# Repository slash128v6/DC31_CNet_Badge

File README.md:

# DC31_CNet_Badge

See the Docs folder

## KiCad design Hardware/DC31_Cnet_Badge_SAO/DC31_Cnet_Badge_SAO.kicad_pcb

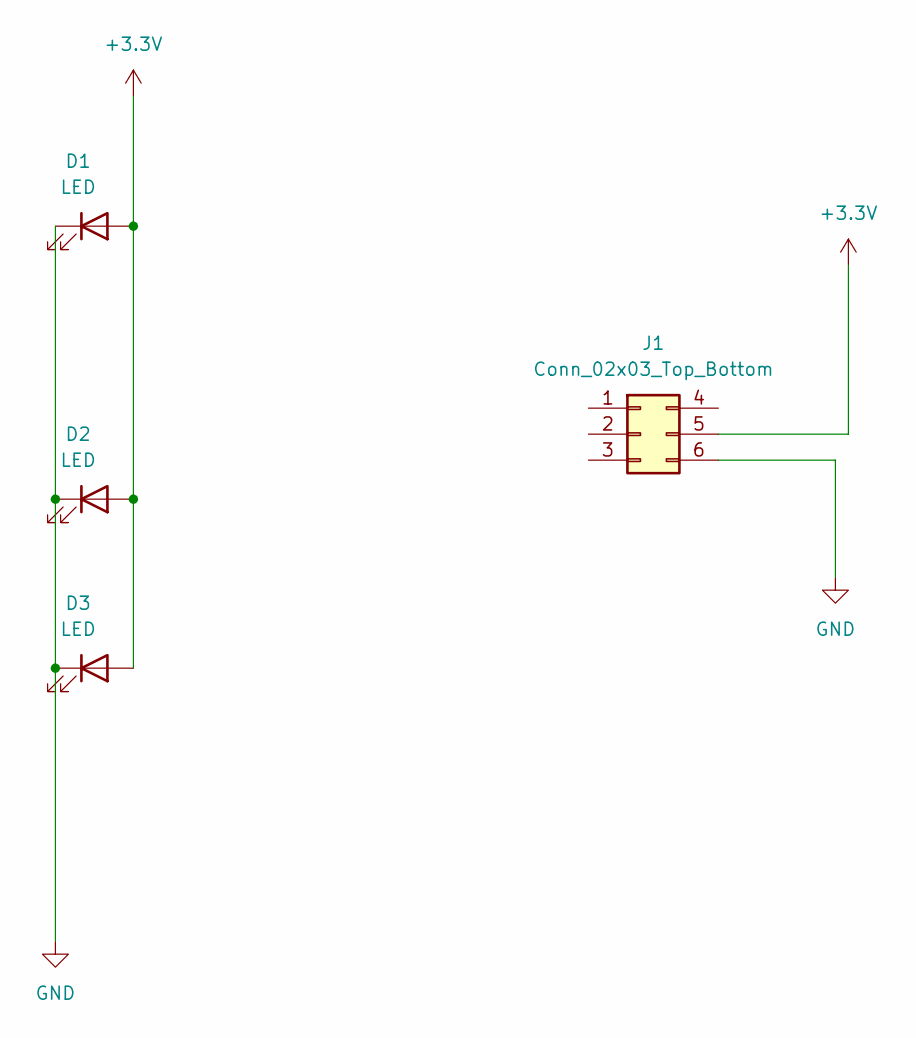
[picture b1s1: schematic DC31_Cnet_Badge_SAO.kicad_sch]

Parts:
D1, D2, D3: LED; LED_D3.0mm
J1: Conn_02x03_Top_Bottom; PinSocket_2x03_P2.54mm_Vertical_Tab

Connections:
+3.3V: D1.2 (A), D2.2 (A), D3.2 (A), J1.5
GND: D1.1 (K), D2.1 (K), D3.1 (K), J1.6

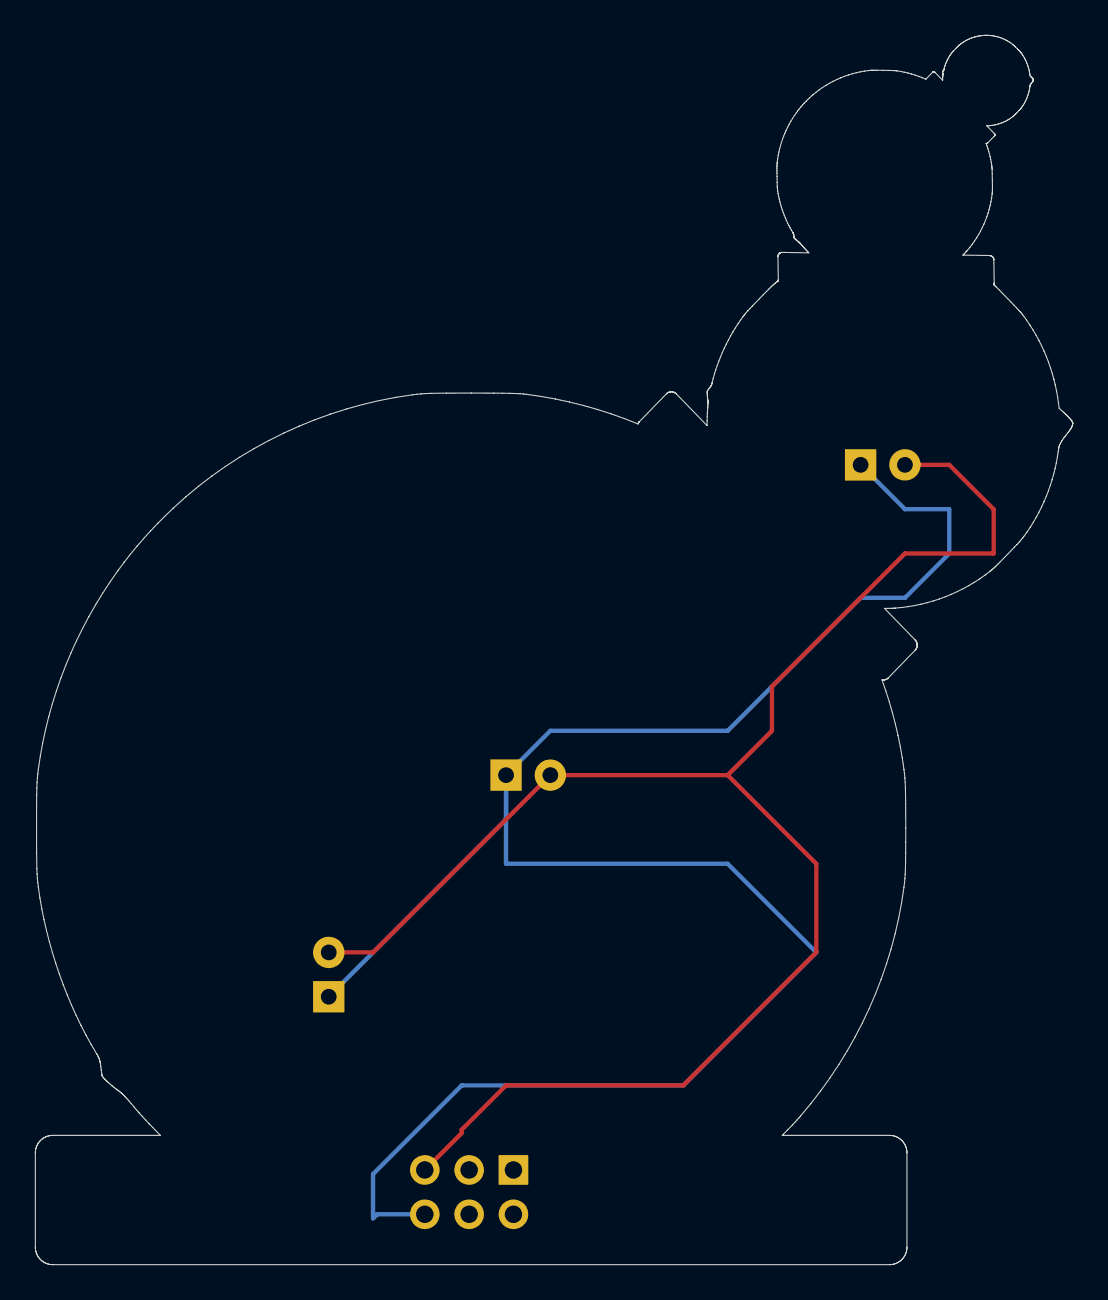
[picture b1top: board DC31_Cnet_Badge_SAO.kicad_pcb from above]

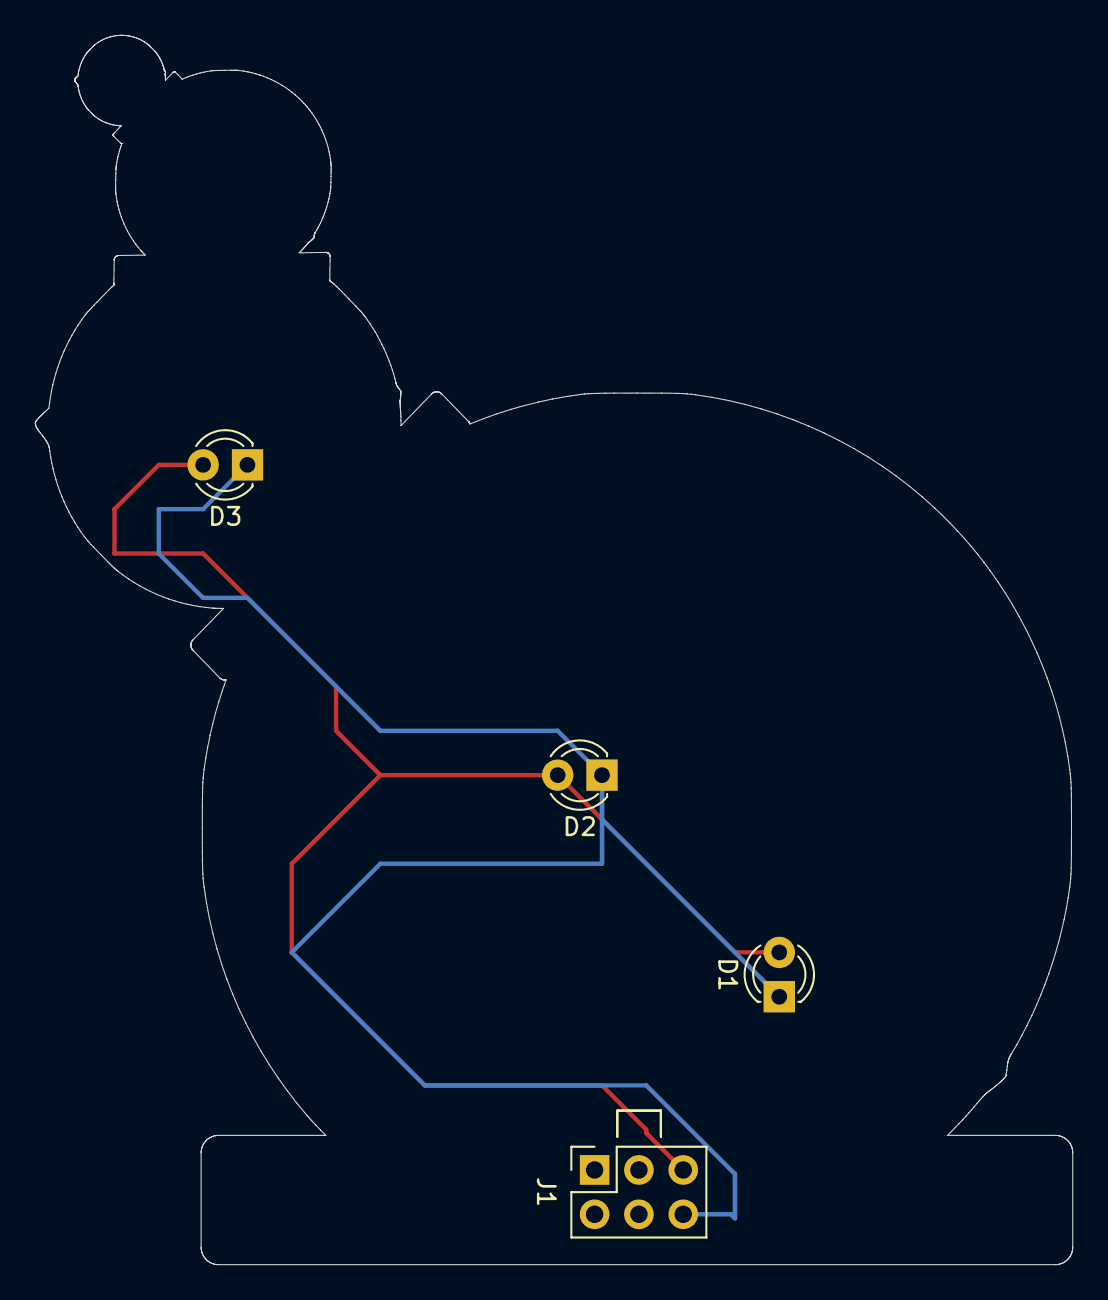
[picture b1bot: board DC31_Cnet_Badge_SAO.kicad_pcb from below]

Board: 2 copper layers, 59.5 x 70.5 mm, 4 parts (4 on the bottom side), 2 nets.

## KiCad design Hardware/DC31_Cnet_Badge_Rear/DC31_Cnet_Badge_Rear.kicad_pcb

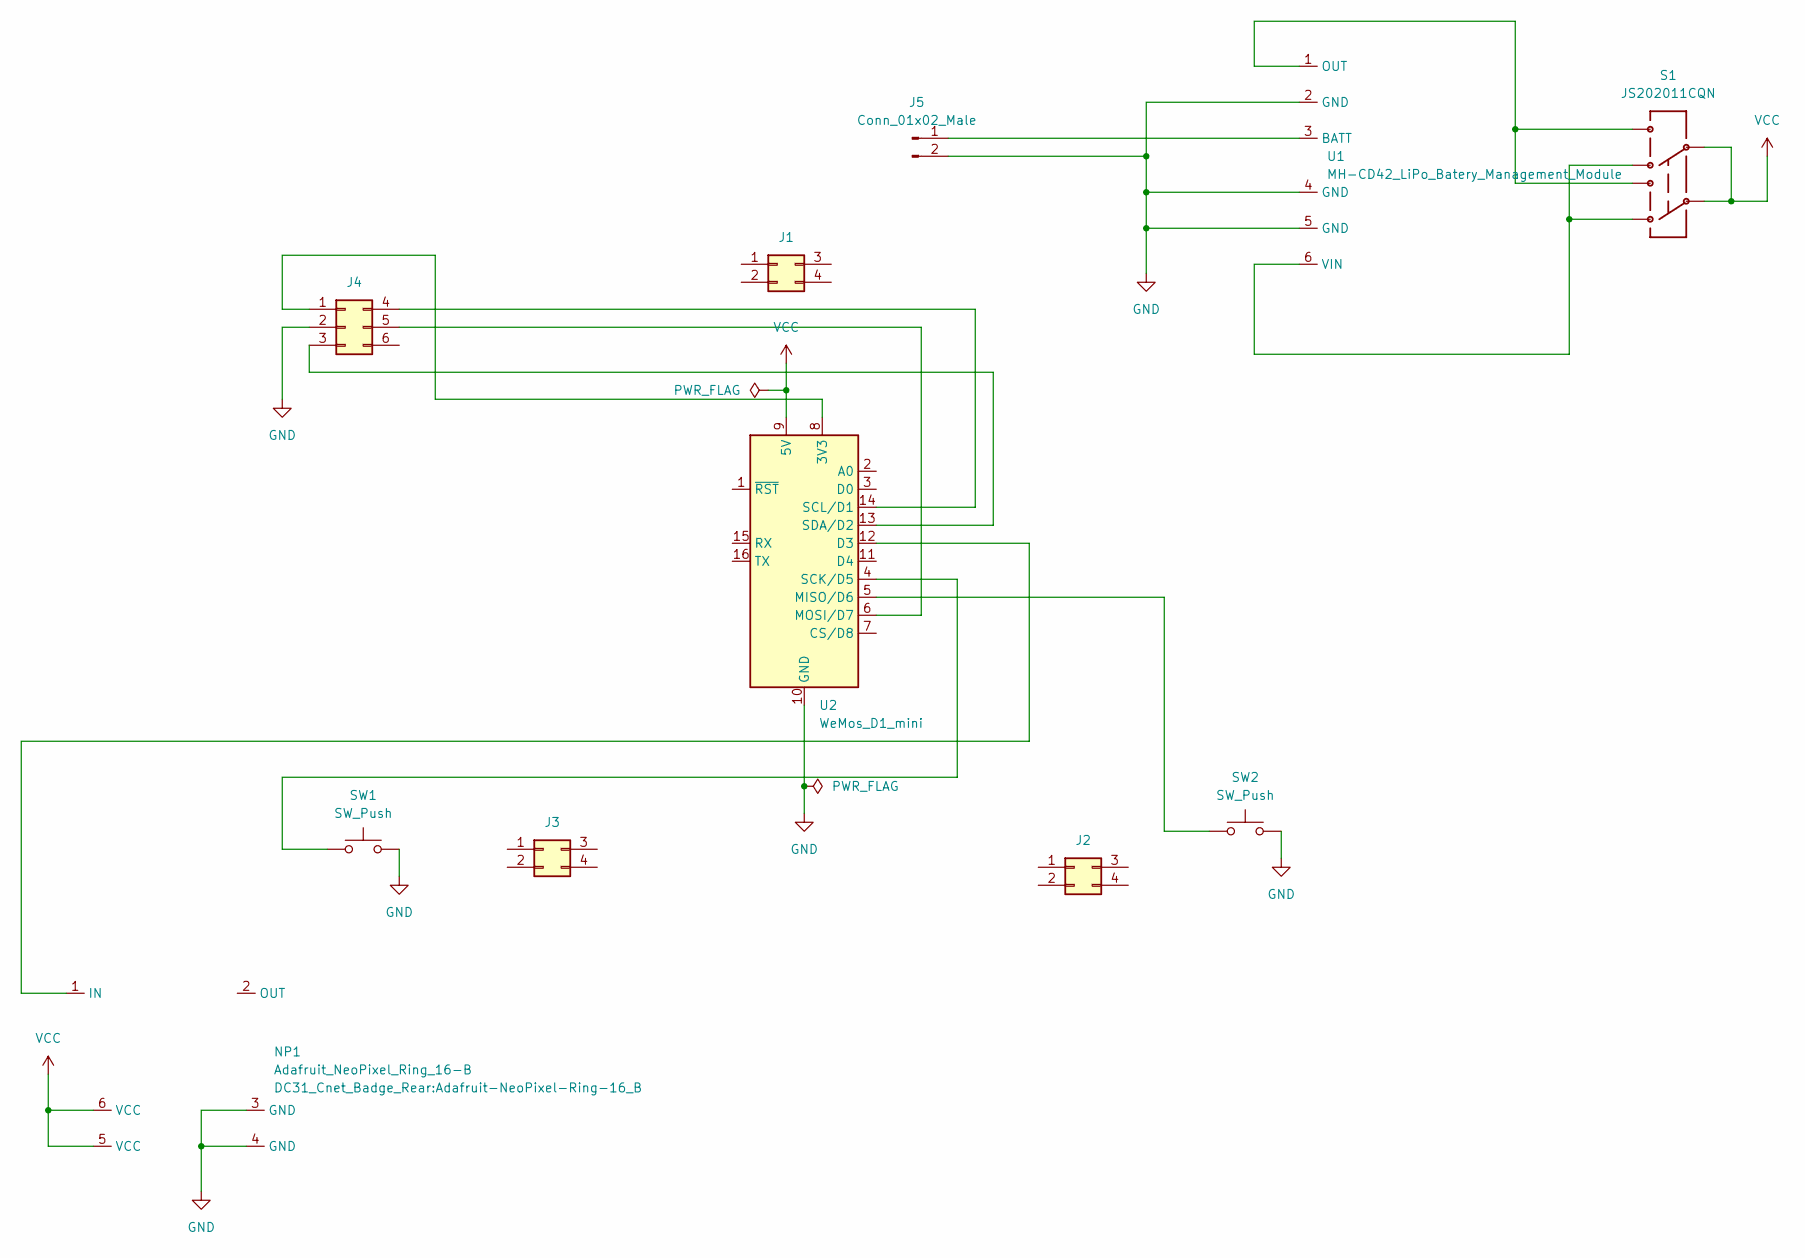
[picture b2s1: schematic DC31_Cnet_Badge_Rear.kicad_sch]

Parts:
J1, J2, J3: Conn_02x02_Top_Bottom; PinSocket_2x02_P2.54mm_Vertical
J4: Conn_02x03_Top_Bottom; PinSocket_2x03_P2.54mm_Vertical_Tab
J5: Conn_01x02_Male; JST_PH_S2B-PH-K_1x02_P2.00mm_Horizontal
NP1: Adafruit_NeoPixel_Ring_16-B; Adafruit-NeoPixel-Ring-16_B
S1: JS202011CQN; SPARKFUN-RETIRED_SWITCH-2.5X3.2-6
SW1, SW2: SW_Push; SW_PUSH_6mm
U1: MH-CD42_LiPo_Batery_Management_Module; MH-CD42 LiPo Battery Management Module Rear Charge LEDs
U2: WeMos_D1_mini; WEMOS_D1_mini_light

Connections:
GND: J4.2, J5.2, NP1.3 (GND), NP1.4 (GND), SW1.2, SW2.2, U1.2 (GND), U1.4 (GND), U1.5 (GND), U2.10 (GND)
unnamed: J4.1, U2.8 (3V3)
unnamed: J4.3, U2.13 (SDA/D2)
unnamed: J4.4, U2.14 (SCL/D1)
unnamed: J4.5, U2.6 (MOSI/D7)
unnamed: J5.1, U1.3 (BATT)
unnamed: NP1.1 (IN), U2.12 (D3)
unnamed: S1.1, S1.4, U1.6 (VIN)
unnamed: S1.3, S1.6, U1.1 (OUT)
unnamed: SW1.1, U2.4 (SCK/D5)
unnamed: SW2.1, U2.5 (MISO/D6)
VCC: NP1.5 (VCC), NP1.6 (VCC), S1.2, S1.5, U2.9 (5V)

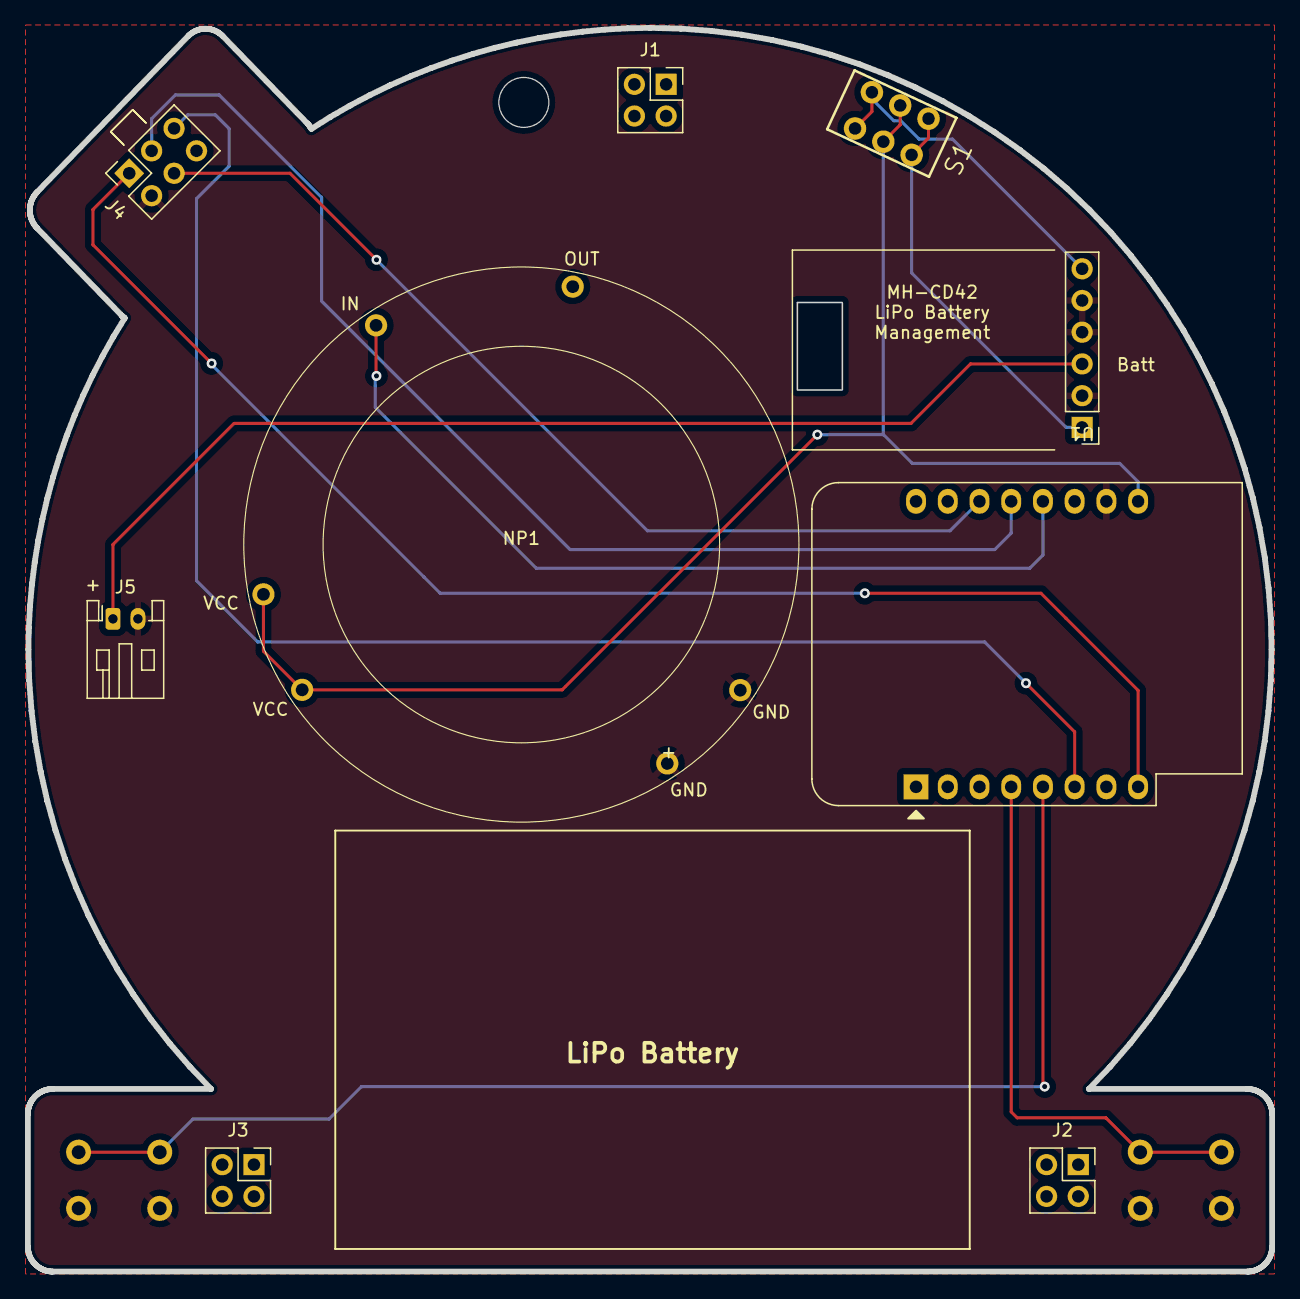
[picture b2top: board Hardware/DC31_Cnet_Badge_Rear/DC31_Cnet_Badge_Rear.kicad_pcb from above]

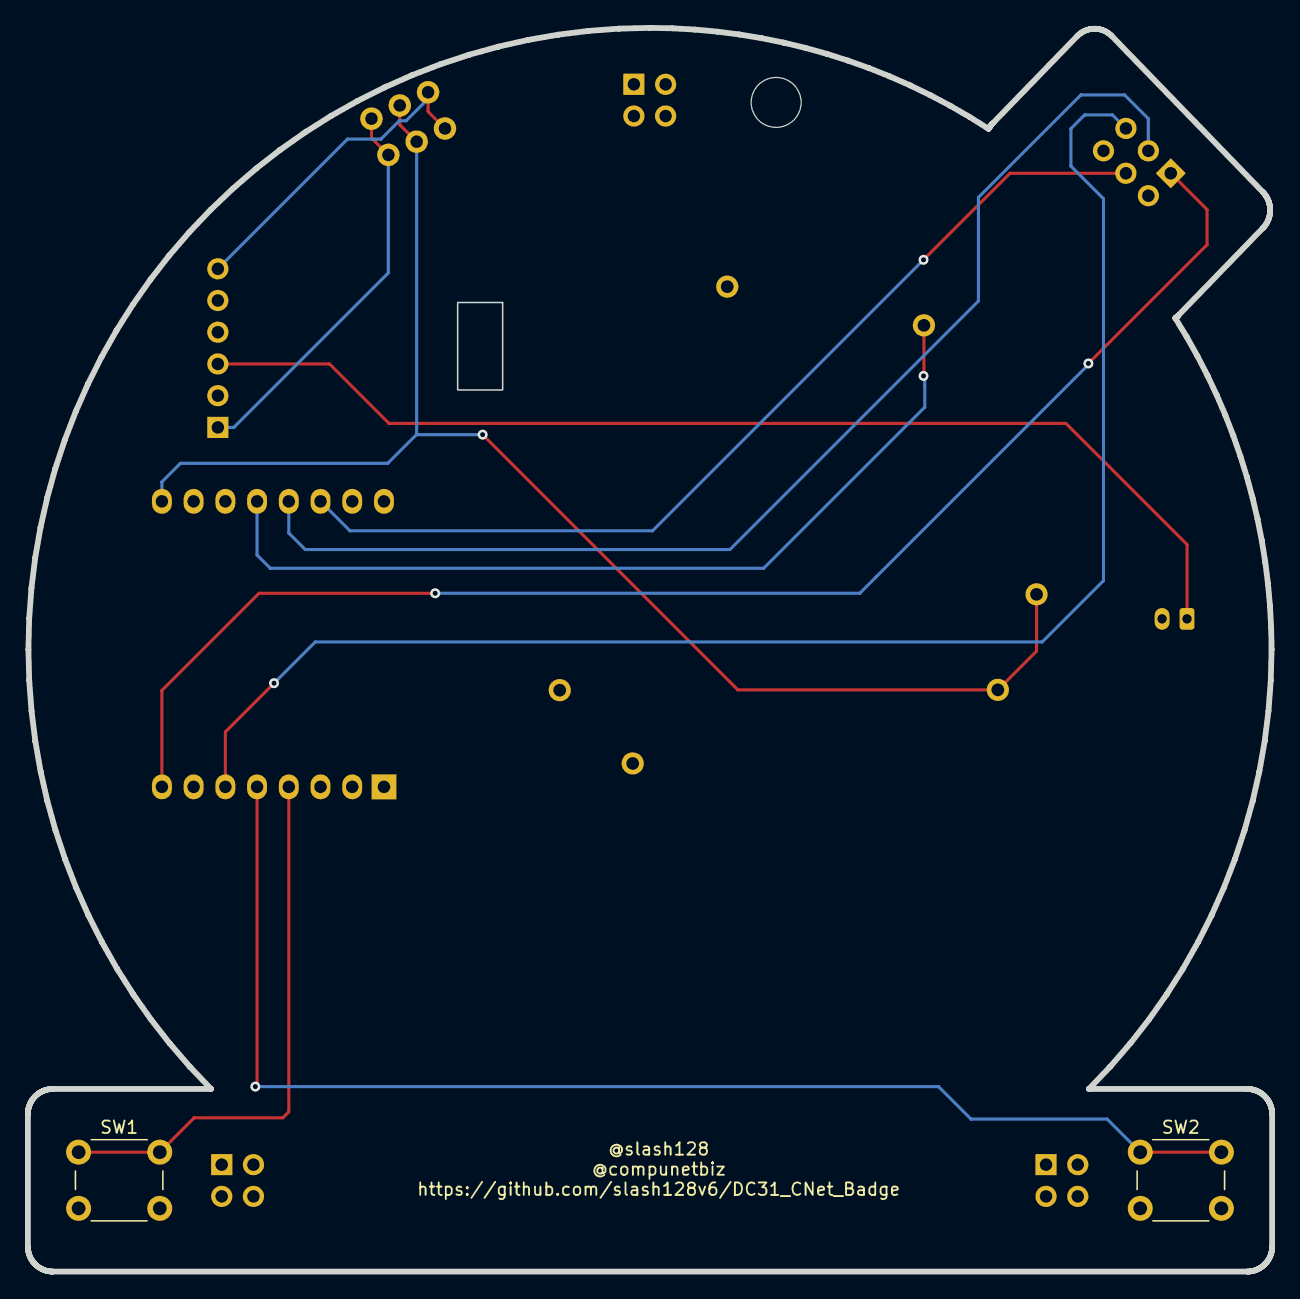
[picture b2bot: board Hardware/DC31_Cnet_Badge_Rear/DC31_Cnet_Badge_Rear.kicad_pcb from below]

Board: 2 copper layers, 99.6 x 99.6 mm, 11 parts (2 on the bottom side), 12 nets.

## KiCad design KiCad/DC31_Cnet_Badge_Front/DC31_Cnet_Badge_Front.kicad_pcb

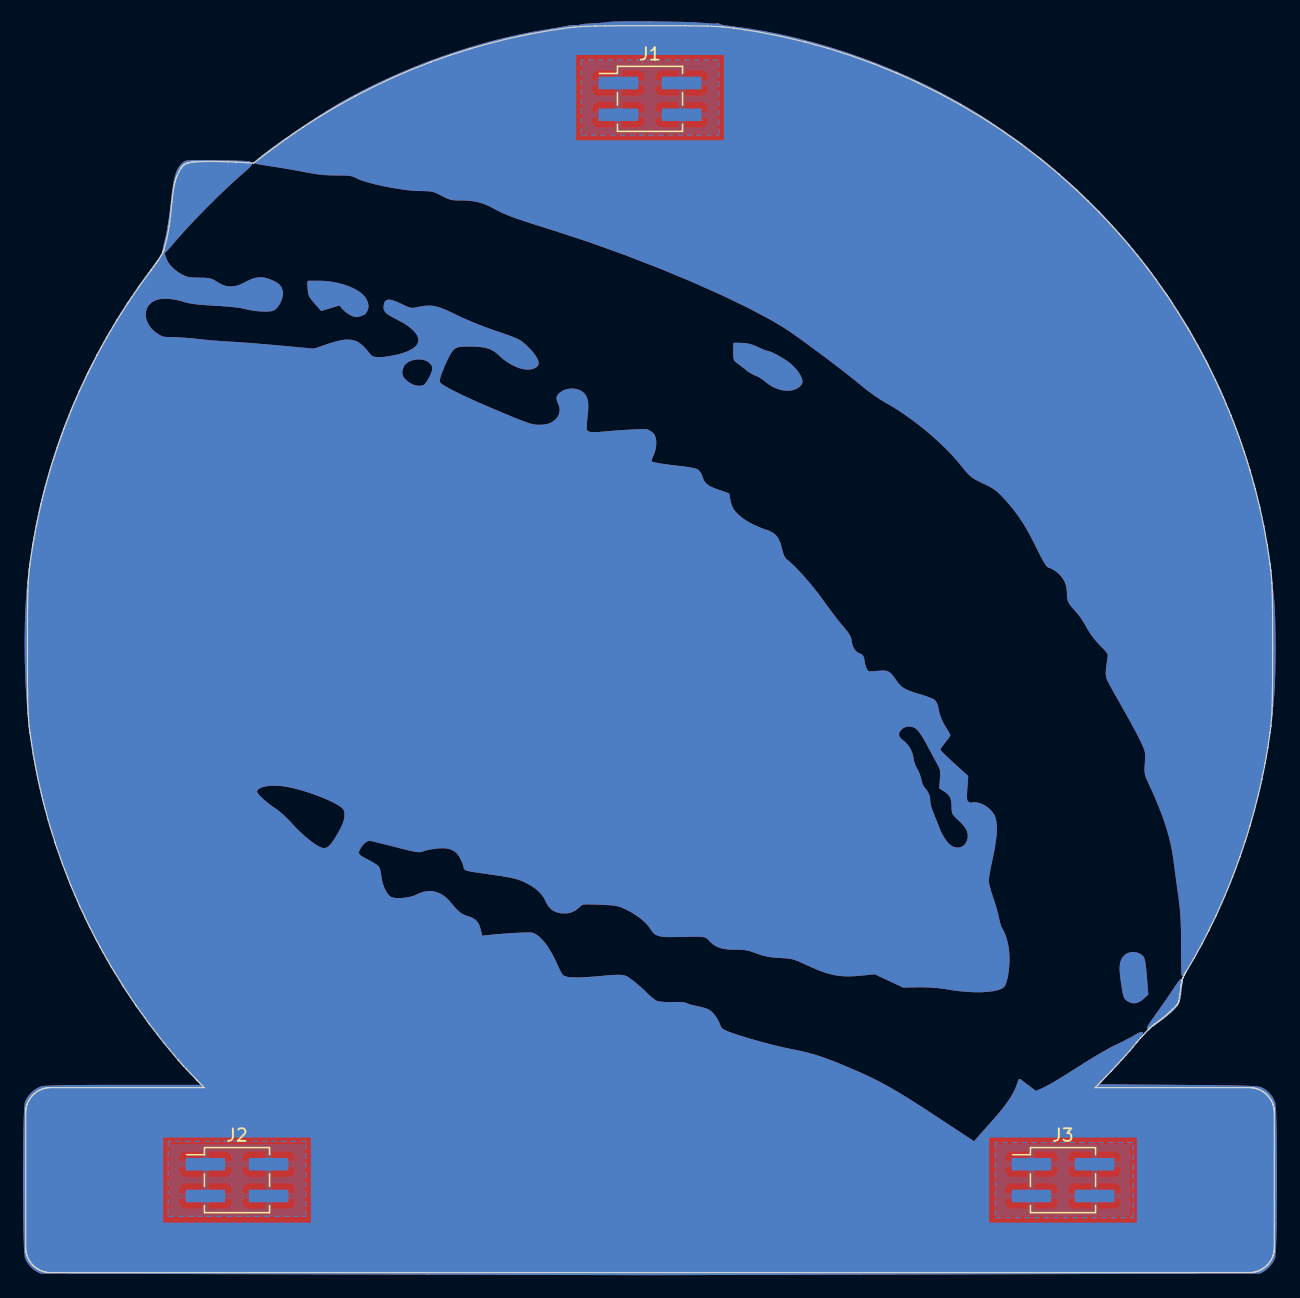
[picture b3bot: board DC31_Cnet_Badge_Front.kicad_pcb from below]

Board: 2 copper layers, 99.8 x 99.6 mm, 3 parts (3 on the bottom side), 3 nets, no tracks yet.

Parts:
J1, J2, J3: Conn_02x02_Top_Bottom; PinHeader_2x02_P2.54mm_Vertical_SMD

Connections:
/J1: J1.1, J1.2, J1.3, J1.4
/J2: J2.1, J2.2, J2.3, J2.4
/J3: J3.1, J3.2, J3.3, J3.4

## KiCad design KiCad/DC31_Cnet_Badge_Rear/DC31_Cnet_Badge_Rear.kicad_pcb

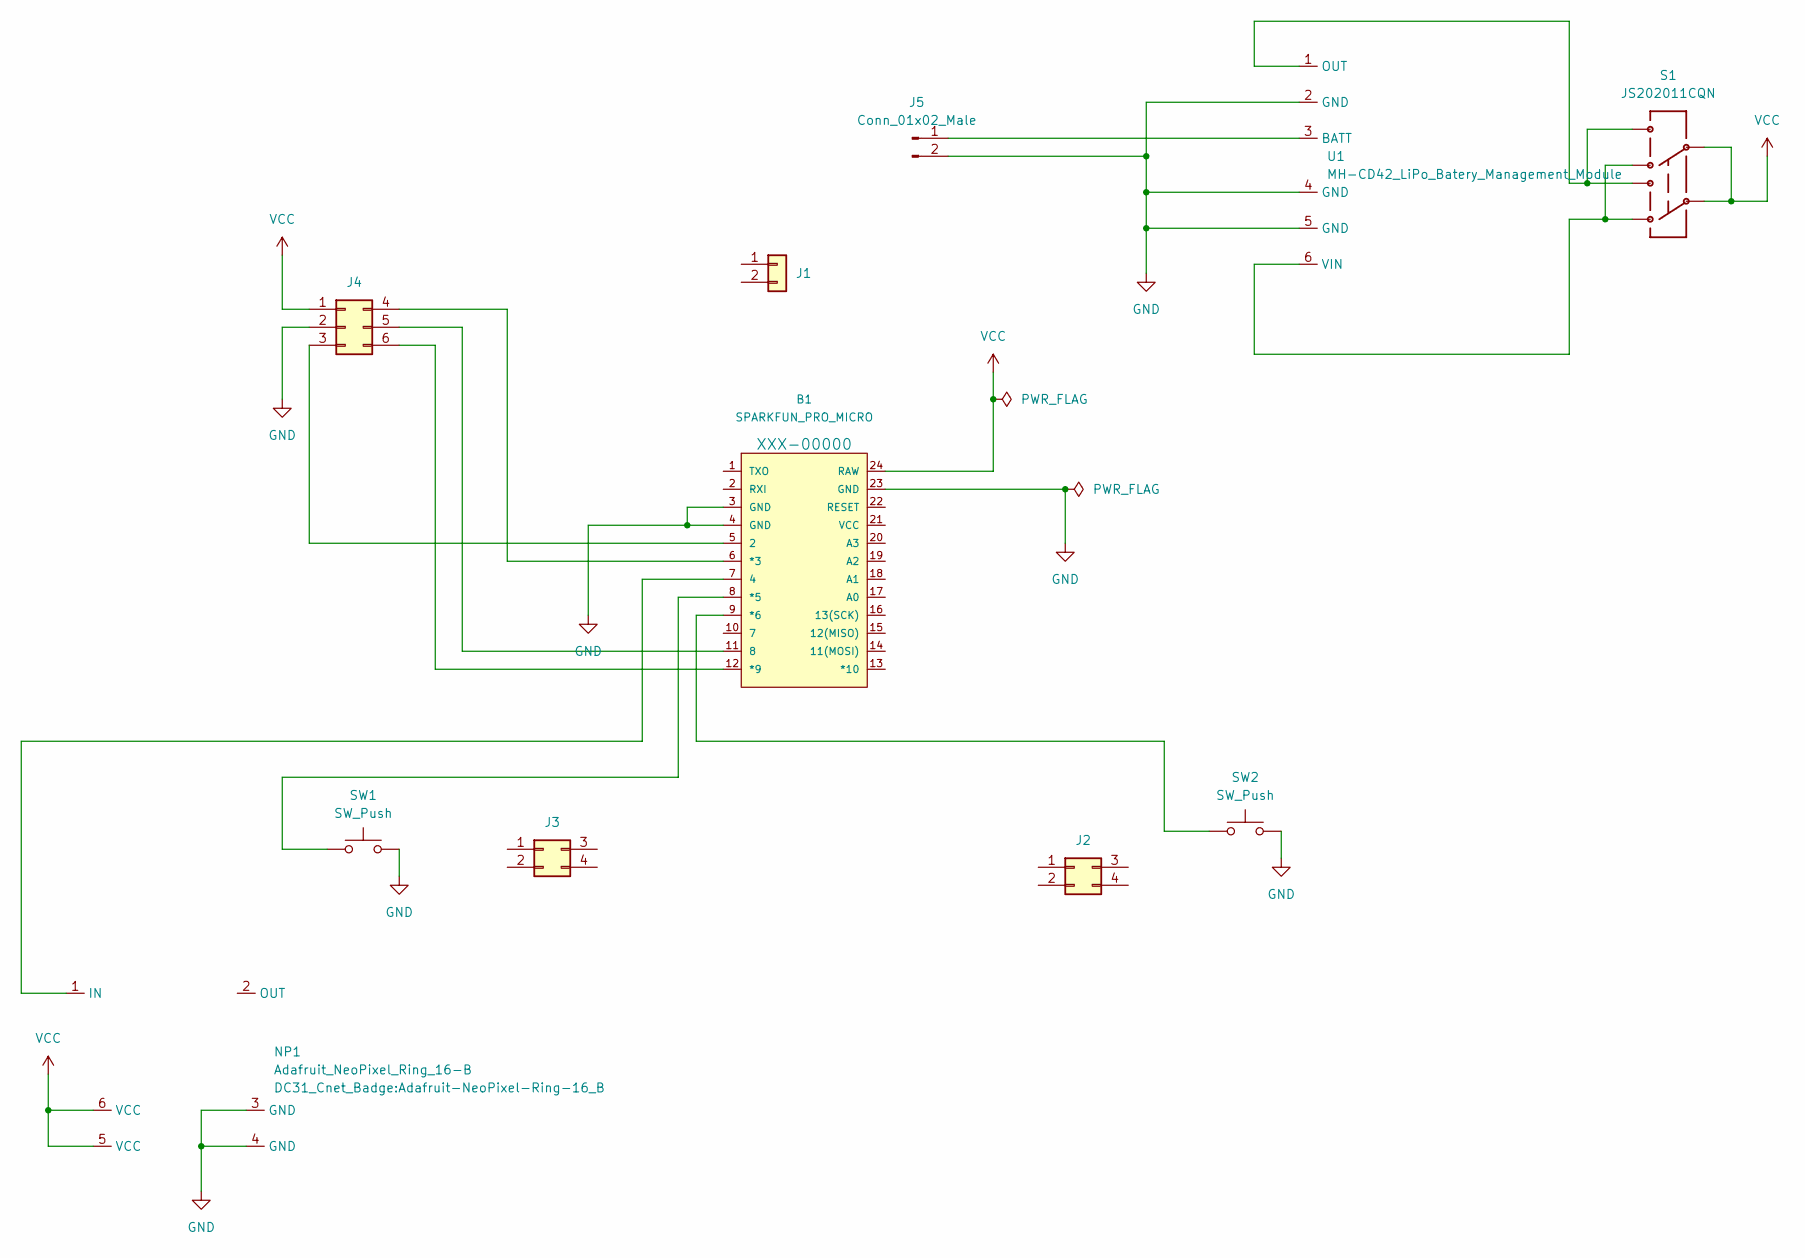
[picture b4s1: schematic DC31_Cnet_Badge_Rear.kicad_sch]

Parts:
B1: SPARKFUN_PRO_MICRO
J1: Conn_02x02_Top_Bottom; PinSocket_1x02_P2.54mm_Vertical
J2, J3: Conn_02x02_Top_Bottom; PinSocket_2x02_P2.54mm_Vertical
J4: Conn_02x03_Top_Bottom; PinSocket_2x03_P2.54mm_Vertical_Tab
J5: Conn_01x02_Male; JST_PH_S2B-PH-K_1x02_P2.00mm_Horizontal
NP1: Adafruit_NeoPixel_Ring_16-B; Adafruit-NeoPixel-Ring-16_B
S1: JS202011CQN; SPARKFUN-RETIRED_SWITCH-2.5X3.2-6
SW1, SW2: SW_Push; SW_PUSH_6mm
U1: MH-CD42_LiPo_Batery_Management_Module; MH-CD42 LiPo Battery Management Module

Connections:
GND: B1.3 (GND), B1.4 (GND), B1.23 (GND), J4.2, J5.2, NP1.3 (GND), NP1.4 (GND), SW1.2, SW2.2, U1.2 (GND), U1.4 (GND), U1.5 (GND)
unnamed: B1.5 (2), J4.3
unnamed: B1.6 (*3), J4.4
unnamed: B1.7 (4), NP1.1 (IN)
unnamed: B1.8 (*5), SW1.1
unnamed: B1.9 (*6), SW2.1
unnamed: B1.11 (8), J4.5
unnamed: B1.12 (*9), J4.6
unnamed: J5.1, U1.3 (BATT)
unnamed: S1.1, S1.4, U1.6 (VIN)
unnamed: S1.3, S1.6, U1.1 (OUT)
VCC: B1.24 (RAW), J4.1, NP1.5 (VCC), NP1.6 (VCC), S1.2, S1.5

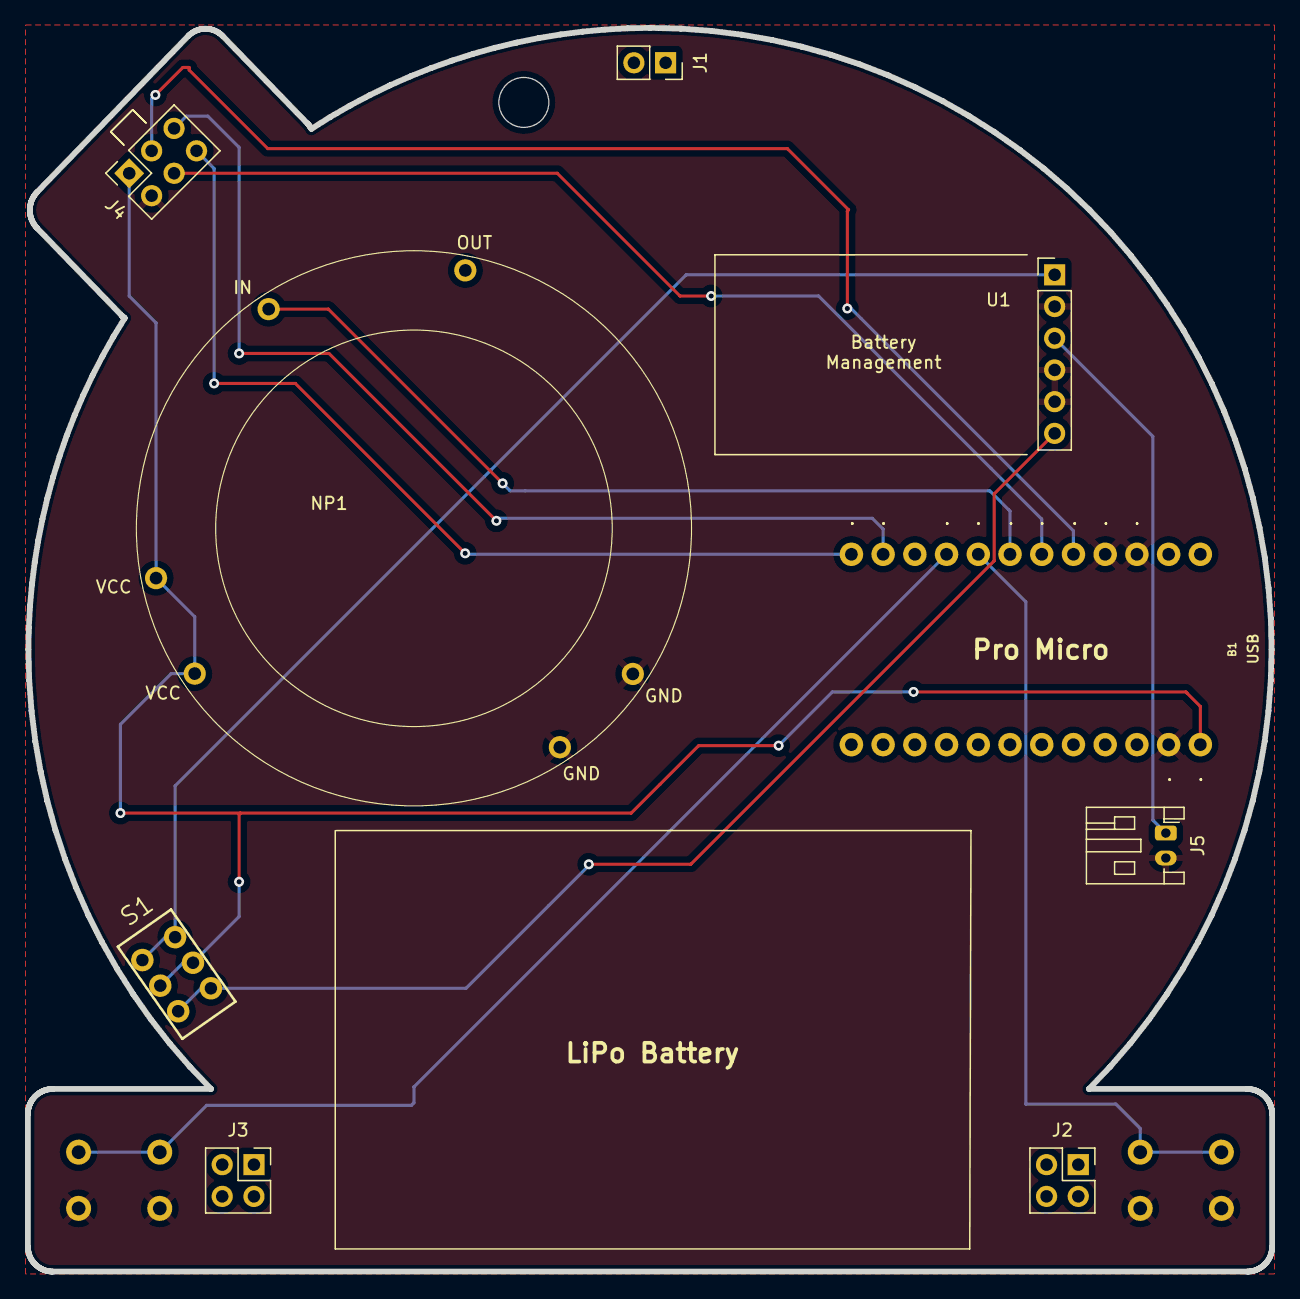
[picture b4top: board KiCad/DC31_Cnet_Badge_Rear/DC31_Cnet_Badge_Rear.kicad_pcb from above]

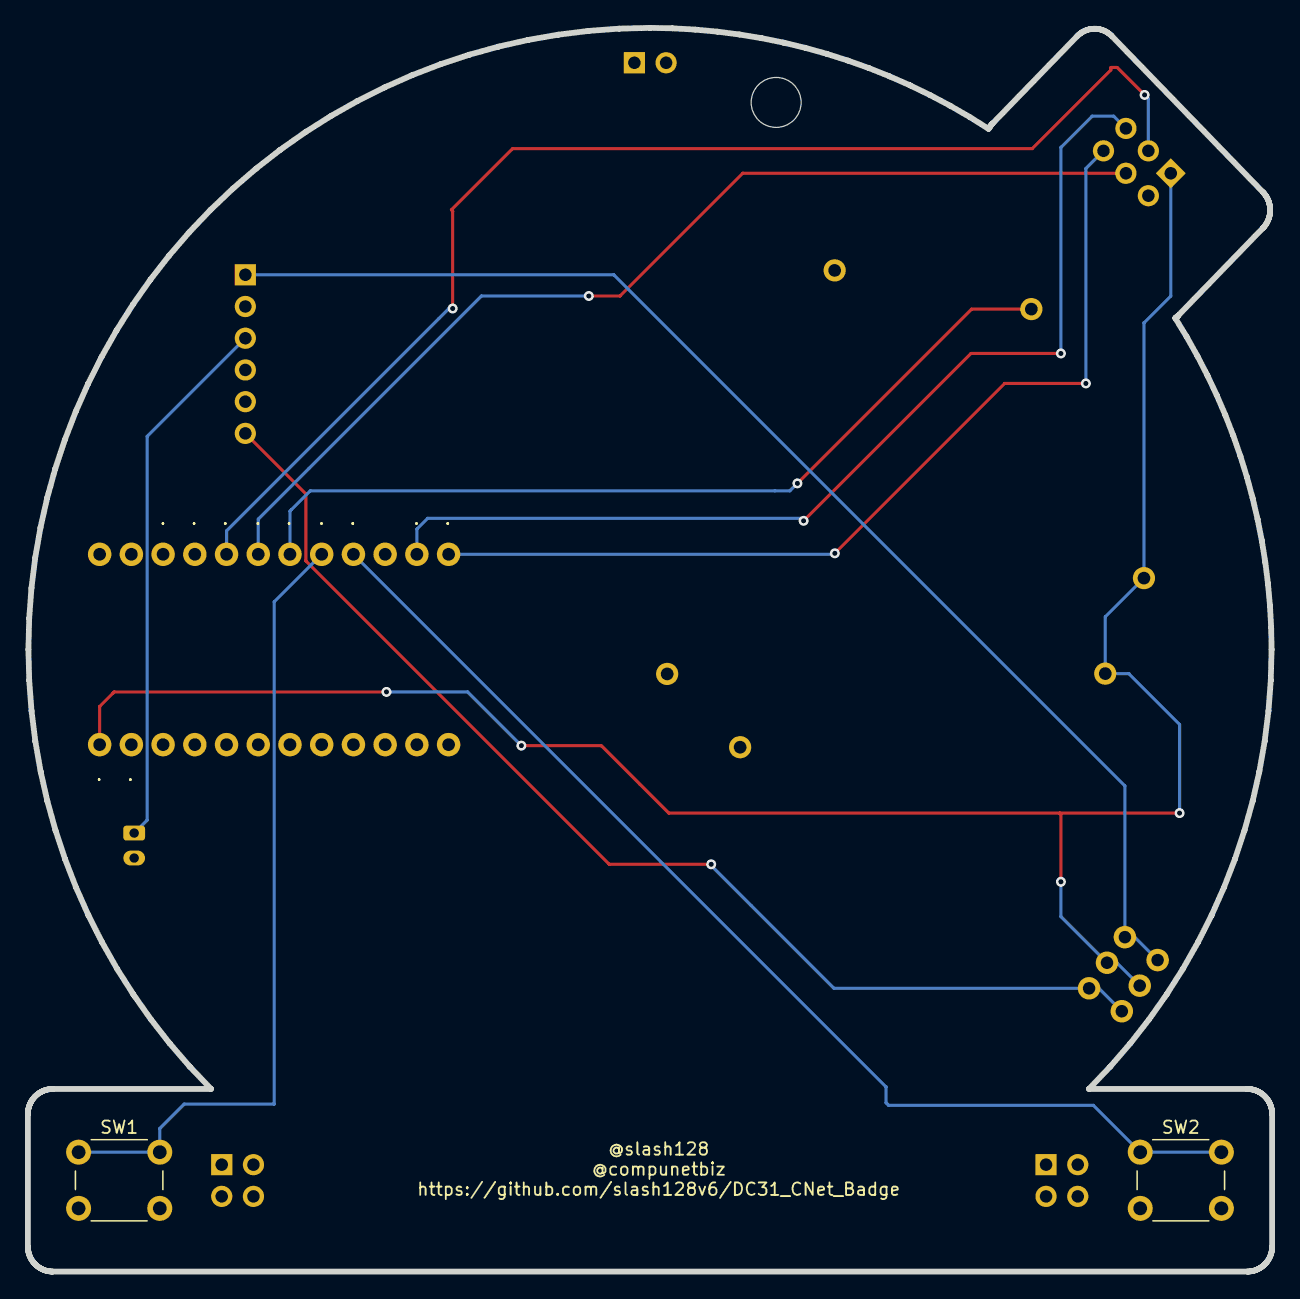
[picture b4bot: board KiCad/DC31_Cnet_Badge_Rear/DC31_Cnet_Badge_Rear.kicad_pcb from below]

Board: 2 copper layers, 99.6 x 99.6 mm, 11 parts (2 on the bottom side), 12 nets.
